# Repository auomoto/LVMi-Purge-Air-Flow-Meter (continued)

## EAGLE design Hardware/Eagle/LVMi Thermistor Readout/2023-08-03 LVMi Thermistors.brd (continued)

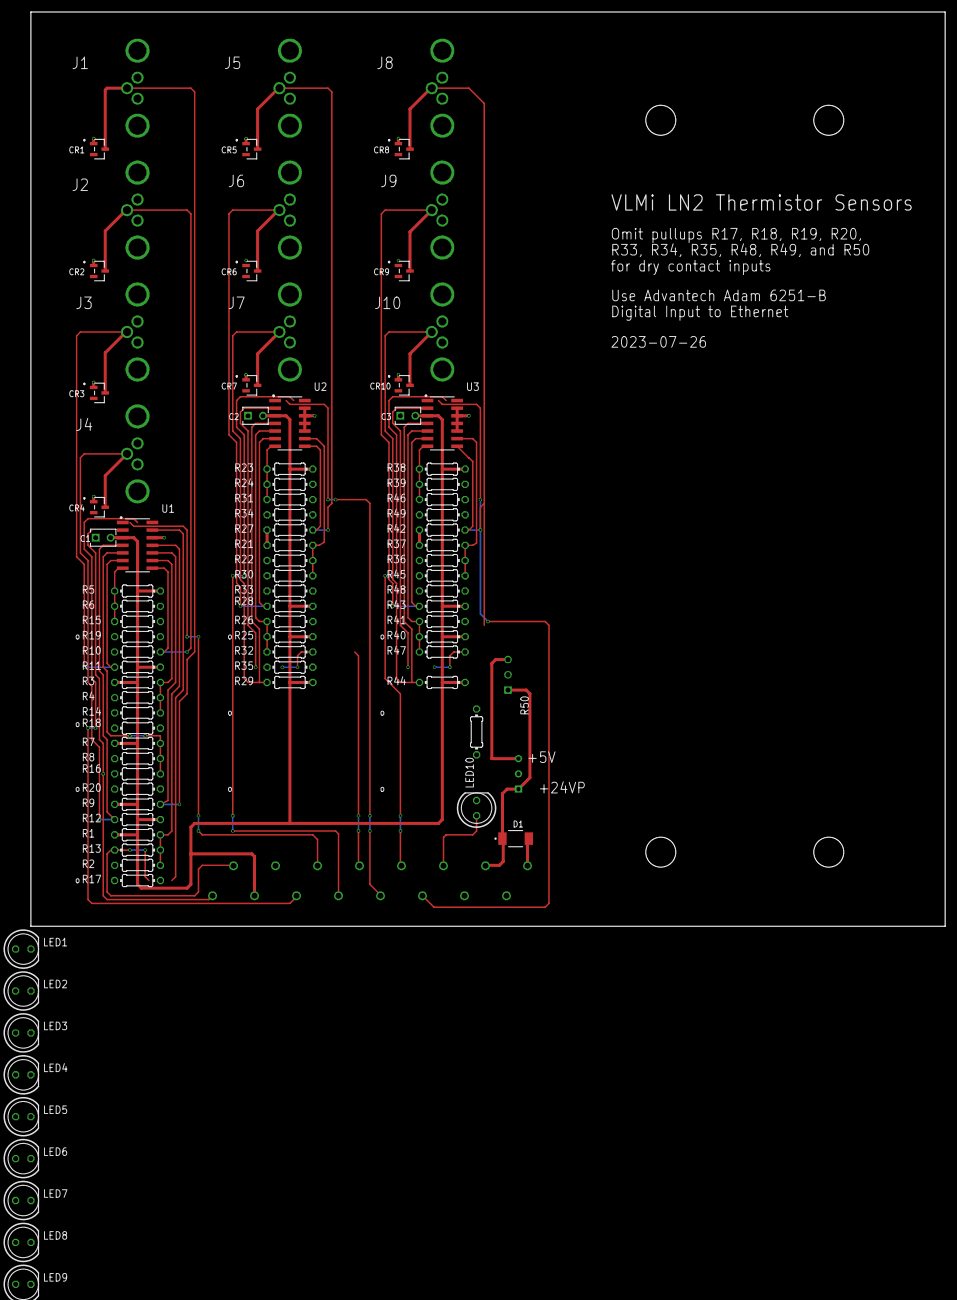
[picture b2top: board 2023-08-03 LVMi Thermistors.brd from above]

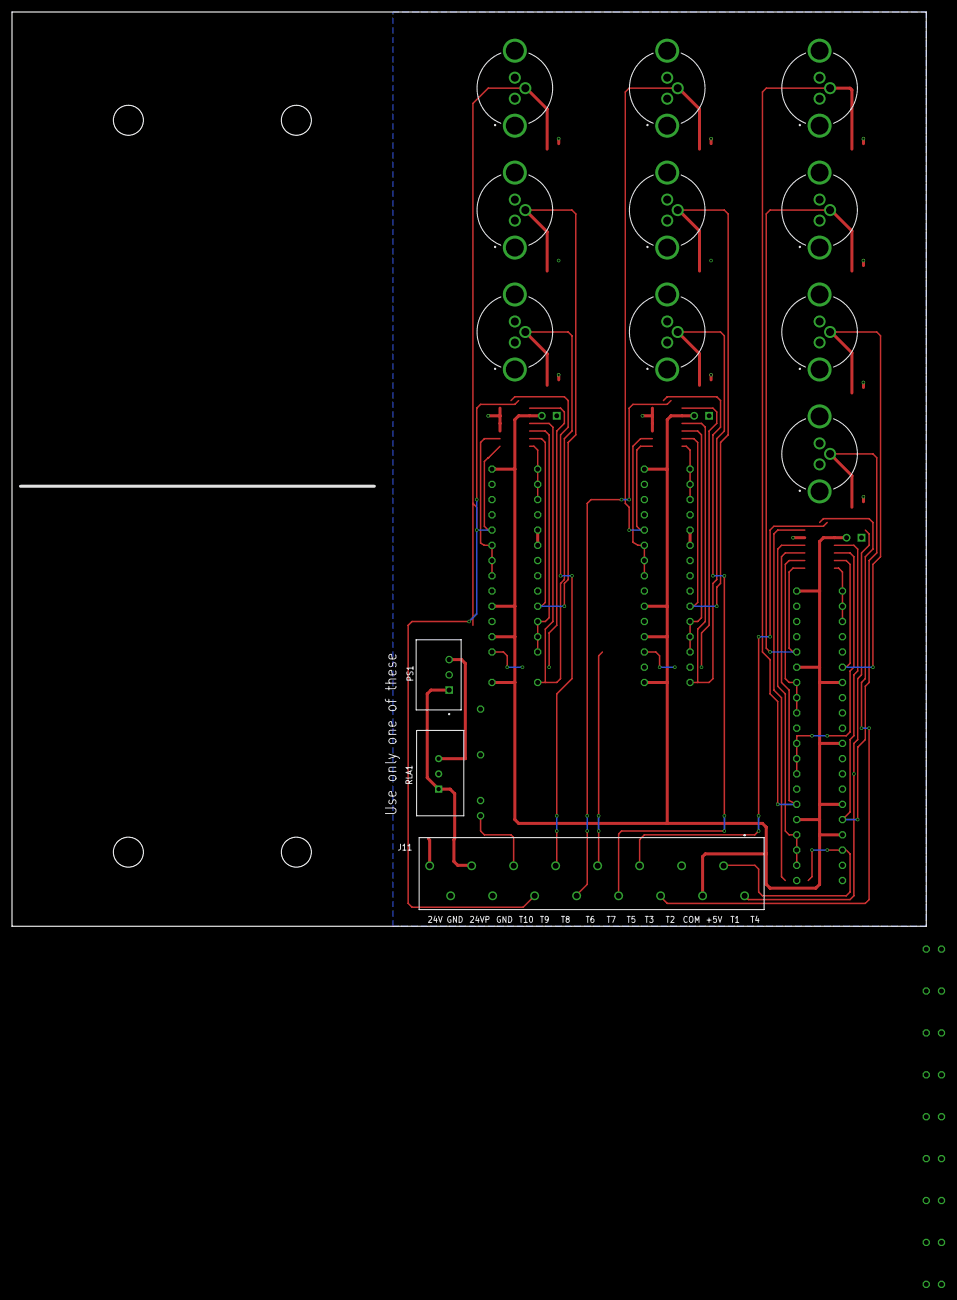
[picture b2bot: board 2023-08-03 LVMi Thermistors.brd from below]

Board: 2 copper layers, 152.4 x 152.4 mm, 90 parts (3 on the bottom side), 34 nets.

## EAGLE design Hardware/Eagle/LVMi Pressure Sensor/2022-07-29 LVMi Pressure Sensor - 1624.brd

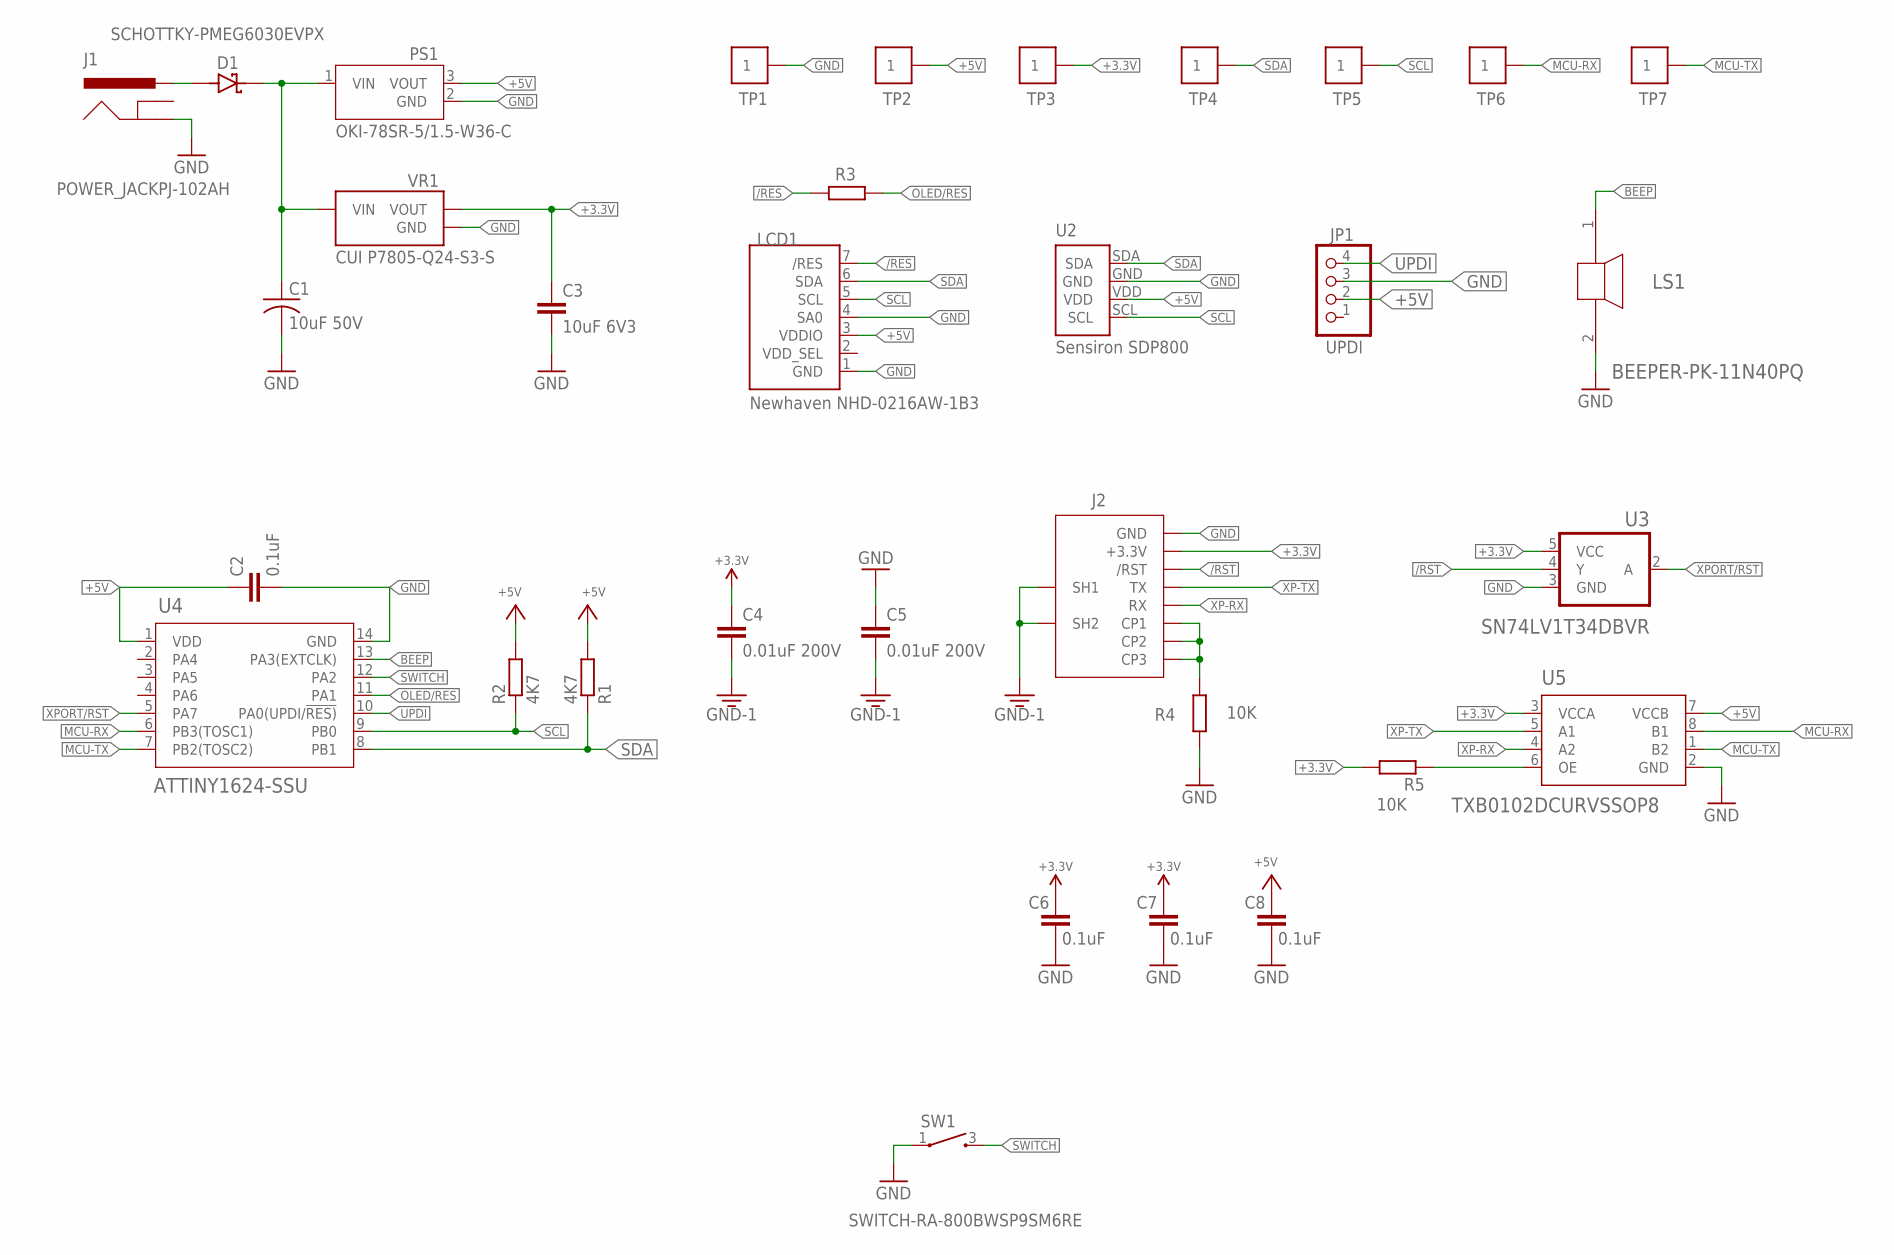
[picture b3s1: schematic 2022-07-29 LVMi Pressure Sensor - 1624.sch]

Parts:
C1: 10uF 50V; C1210
C2, C6, C7, C8: 0.1uF; C0805
C3: 10uF 6V3; C0805
C4, C5: 0.01uF 200V; C0805
D1: SCHOTTKY-PMEG6030EVPX; DIO_PMEG6030EVPX
J1: POWER_JACKPJ-102AH; PJ-102AH
J2: XPORTXPORT-2; XPORT-2
JP1: UPDI; 1X04/90
LCD1: Newhaven NHD-0216AW-1B3; LCD-NEWHAVEN-16X2
LS1: BEEPER-PK-11N40PQ; PK-11N40PQ_MAL
PS1: OKI-78SR-5/1.5-W36-C; CONV_OKI-78SR-5/1.5-W36-C
R1, R2: 4K7; R0805
R3: R-EU_R0805; R0805
R4, R5: 10K; R0805
SW1: SWITCH-RA-800BWSP9SM6RE
TP1: GND; TP5000-TESTPOINT-BLK
TP2: +5V; TP5000-TESTPOINT-RED
TP3: +3.3V; TP5000-TESTPOINT-PUR
TP4: SDA; TP5000-TESTPOINT-YEL
TP5: SCL; TP5000-TESTPOINT-WHI
TP6: MCU-RX; TP5000-TESTPOINT-WHI
TP7: MCU-TX; TP5000-TESTPOINT-WHI
U2: Sensiron SDP800; SDP800_PRESSURE_SENSOR
U3: SN74LV1T34DBVR; SOT95P280X145-5N
U4: ATTINY1624-SSU; SOIC150-14_MCH-M
U5: TXB0102DCURVSSOP8; GHI-IC_VSSOP8(TI)
VR1: CUI P7805-Q24-S3-S; CONV_P7805-Q24-S3-S

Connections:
+3.3V: C3.1, C4.1, C6.2, C7.2, J2.3.3V (+3.3V), R5.2, TP3.P$1, U3.5 (VCC), U5.3 (VCCA), VR1.VOUT
+5V: C2.1, C8.2, JP1.2, LCD1.3 (VDDIO), PS1.3 (VOUT), R1.2, R2.2, TP2.P$1, U2.VDD, U4.1 (VDD), U5.7 (VCCB)
/RES: LCD1.7 (/RES), R3.2
/RST: J2./RST, U3.4 (Y)
BEEP: LS1.1, U4.13 (PA3(EXTCLK))
GND: C1.2, C2.2, C3.2, C5.1, C6.1, C7.1, C8.1, J1.GND, J2.GND, JP1.3, LCD1.1 (GND), LCD1.4 (SA0), LS1.2, PS1.2 (GND), R4.2, SW1.1, TP1.P$1, U2.GND, U3.3 (GND), U4.14 (GND), U5.2 (GND), VR1.GND
GND-1: C4.2, C5.2, J2.P$1 (SH1), J2.P$2 (SH2)
MCU-RX: TP6.P$1, U4.6 (PB3(TOSC1)), U5.8 (B1)
MCU-TX: TP7.P$1, U4.7 (PB2(TOSC2)), U5.1 (B2)
OE: R5.1, U5.6 (OE)
OLED/RES: R3.1, U4.11 (PA1)
SCL: LCD1.5 (SCL), R2.1, TP5.P$1, U2.SCL, U4.9 (PB0)
SDA: LCD1.6 (SDA), R1.1, TP4.P$1, U2.SDA, U4.8 (PB1)
SWITCH: SW1.3 (2), U4.12 (PA2)
UPDI: JP1.4, U4.10 (PA0(UPDI/!RES))
VIN: C1.1, D1.1 (K), PS1.1 (VIN), VR1.VIN
VSUP: D1.2 (A), J1.PWR
XP-CP: J2.CP1, J2.CP2, J2.CP3, R4.1
XP-RX: J2.RX, U5.4 (A2)
XP-TX: J2.TX, U5.5 (A1)
XPORT/RST: U3.2 (A), U4.5 (PA7)

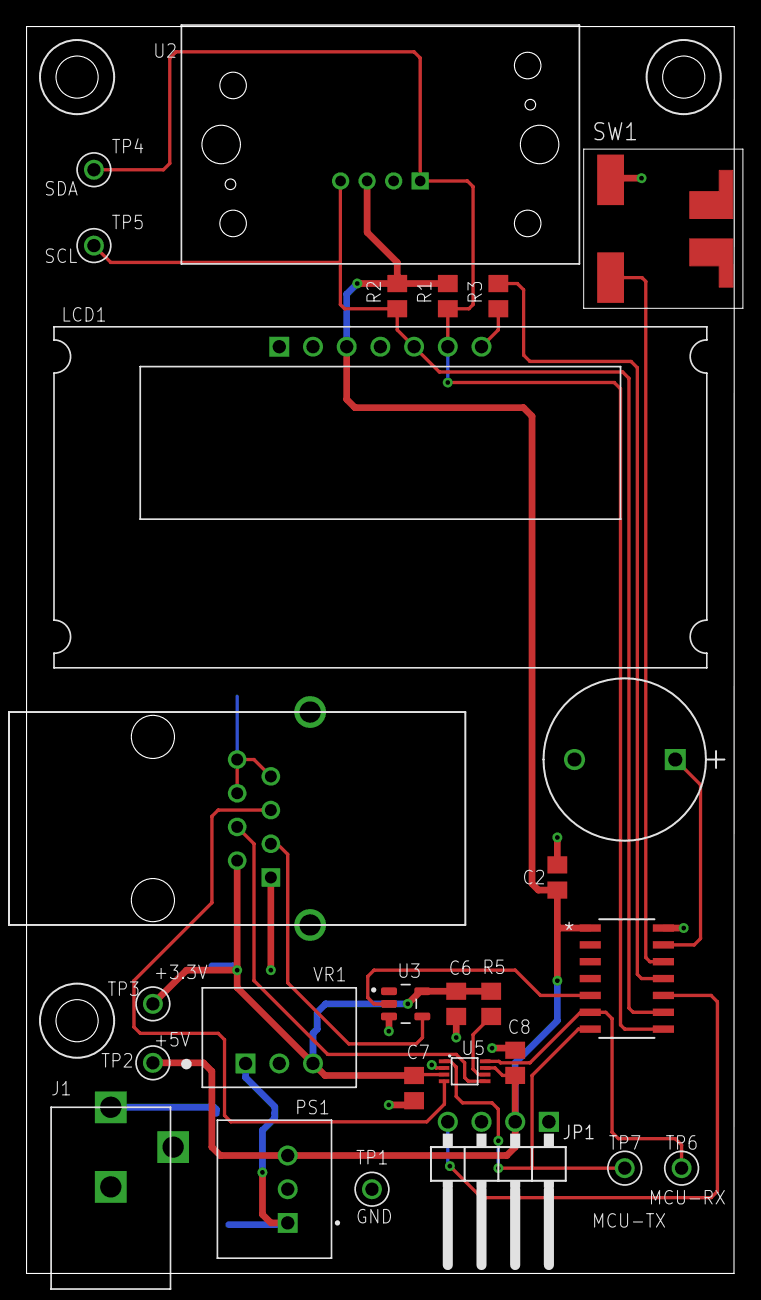
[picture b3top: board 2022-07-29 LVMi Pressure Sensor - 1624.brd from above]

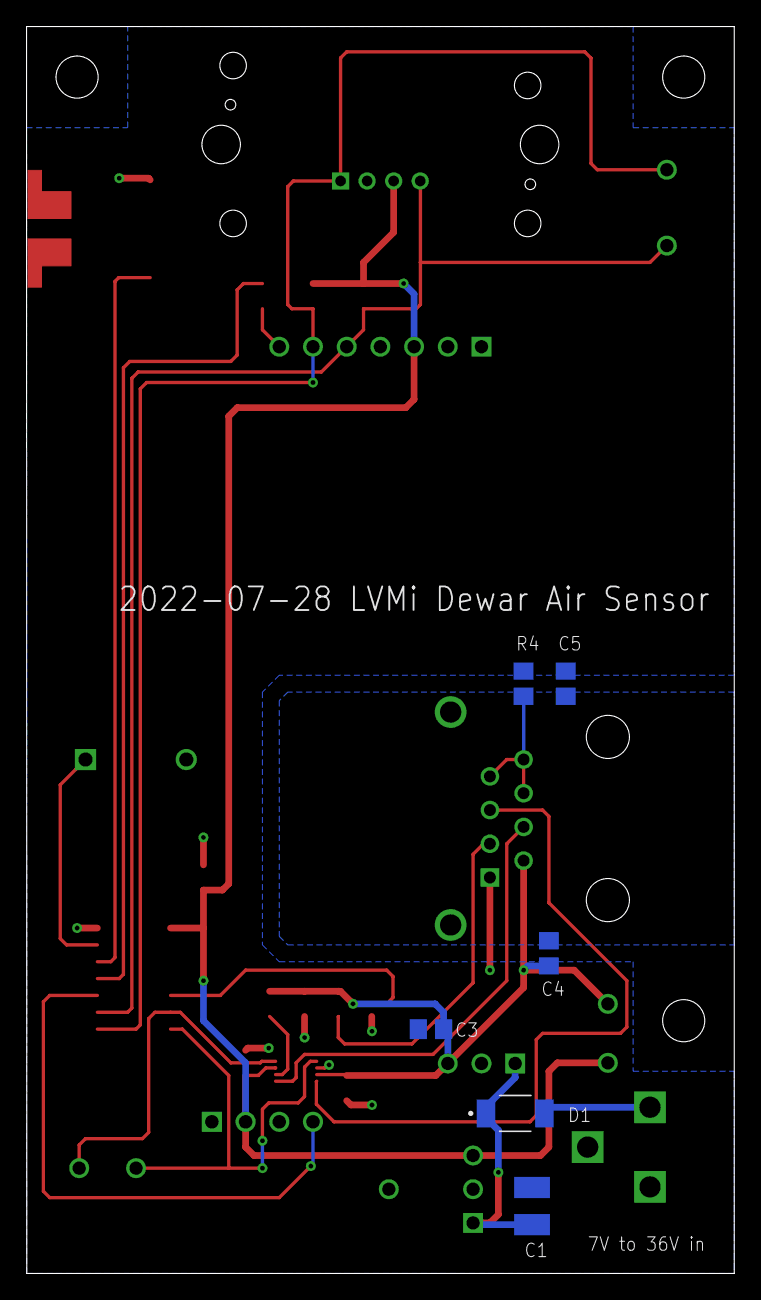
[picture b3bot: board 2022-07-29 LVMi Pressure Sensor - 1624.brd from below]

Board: 2 copper layers, 53.3 x 94.0 mm, 33 parts (6 on the bottom side), 21 nets.

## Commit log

2022-07-28 Switched to ATtiny1624
2024-01-11 Initial load
